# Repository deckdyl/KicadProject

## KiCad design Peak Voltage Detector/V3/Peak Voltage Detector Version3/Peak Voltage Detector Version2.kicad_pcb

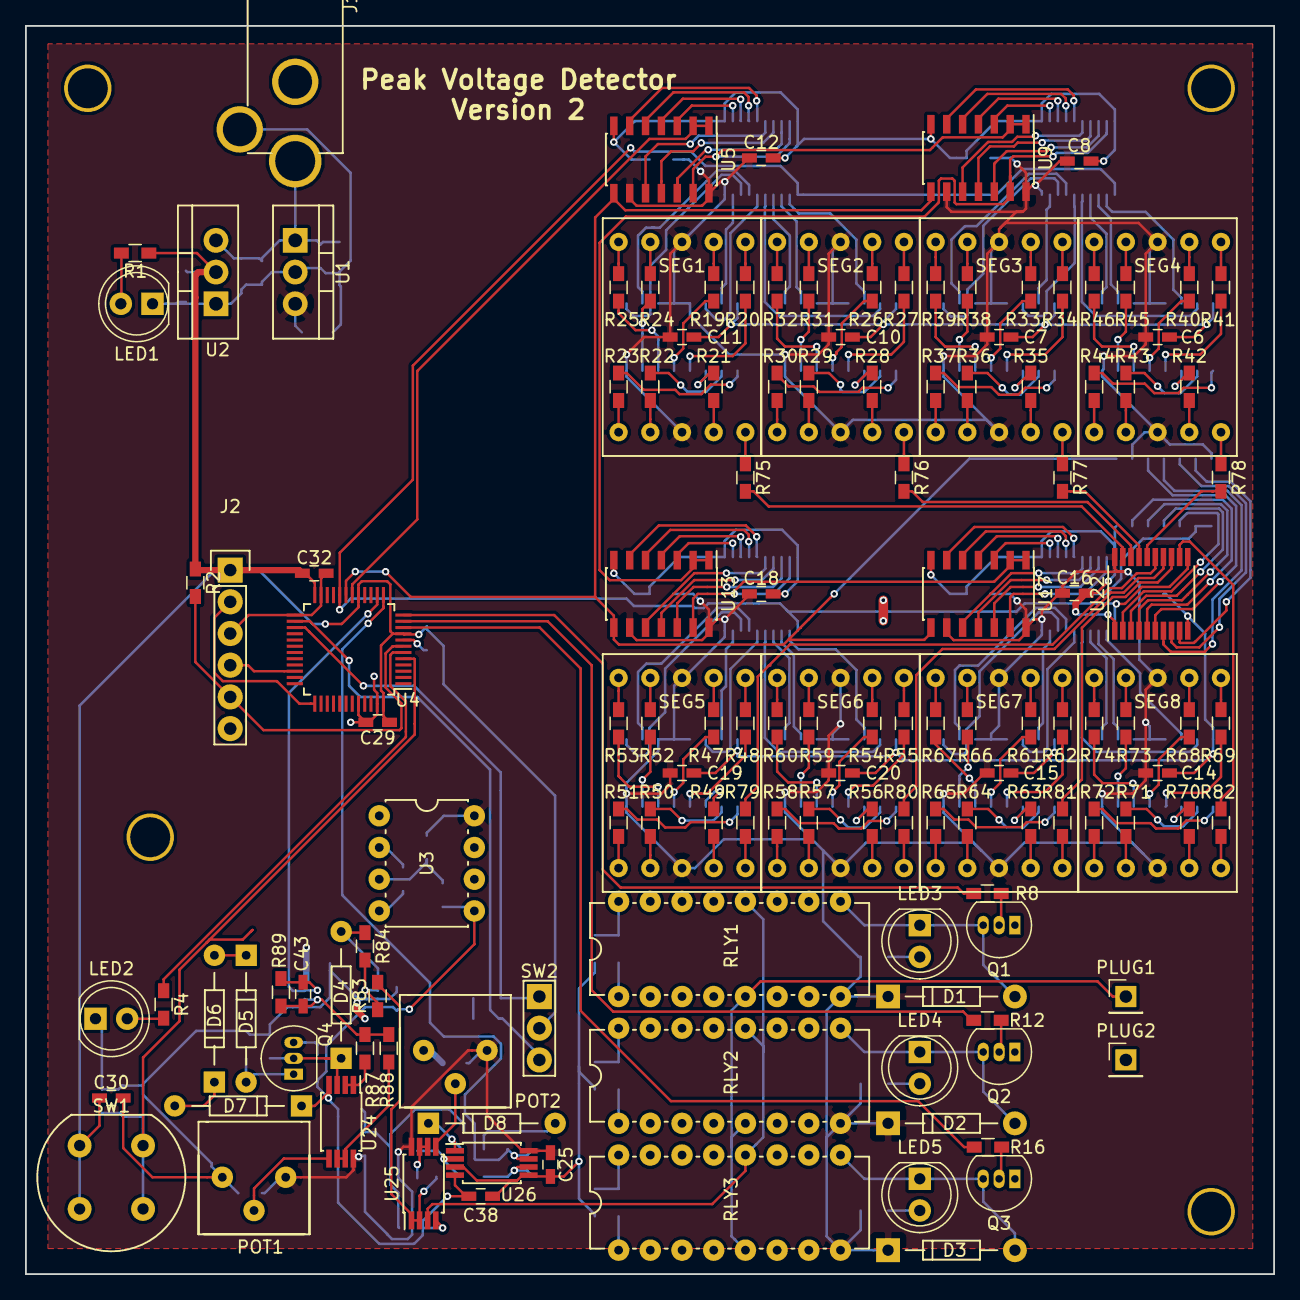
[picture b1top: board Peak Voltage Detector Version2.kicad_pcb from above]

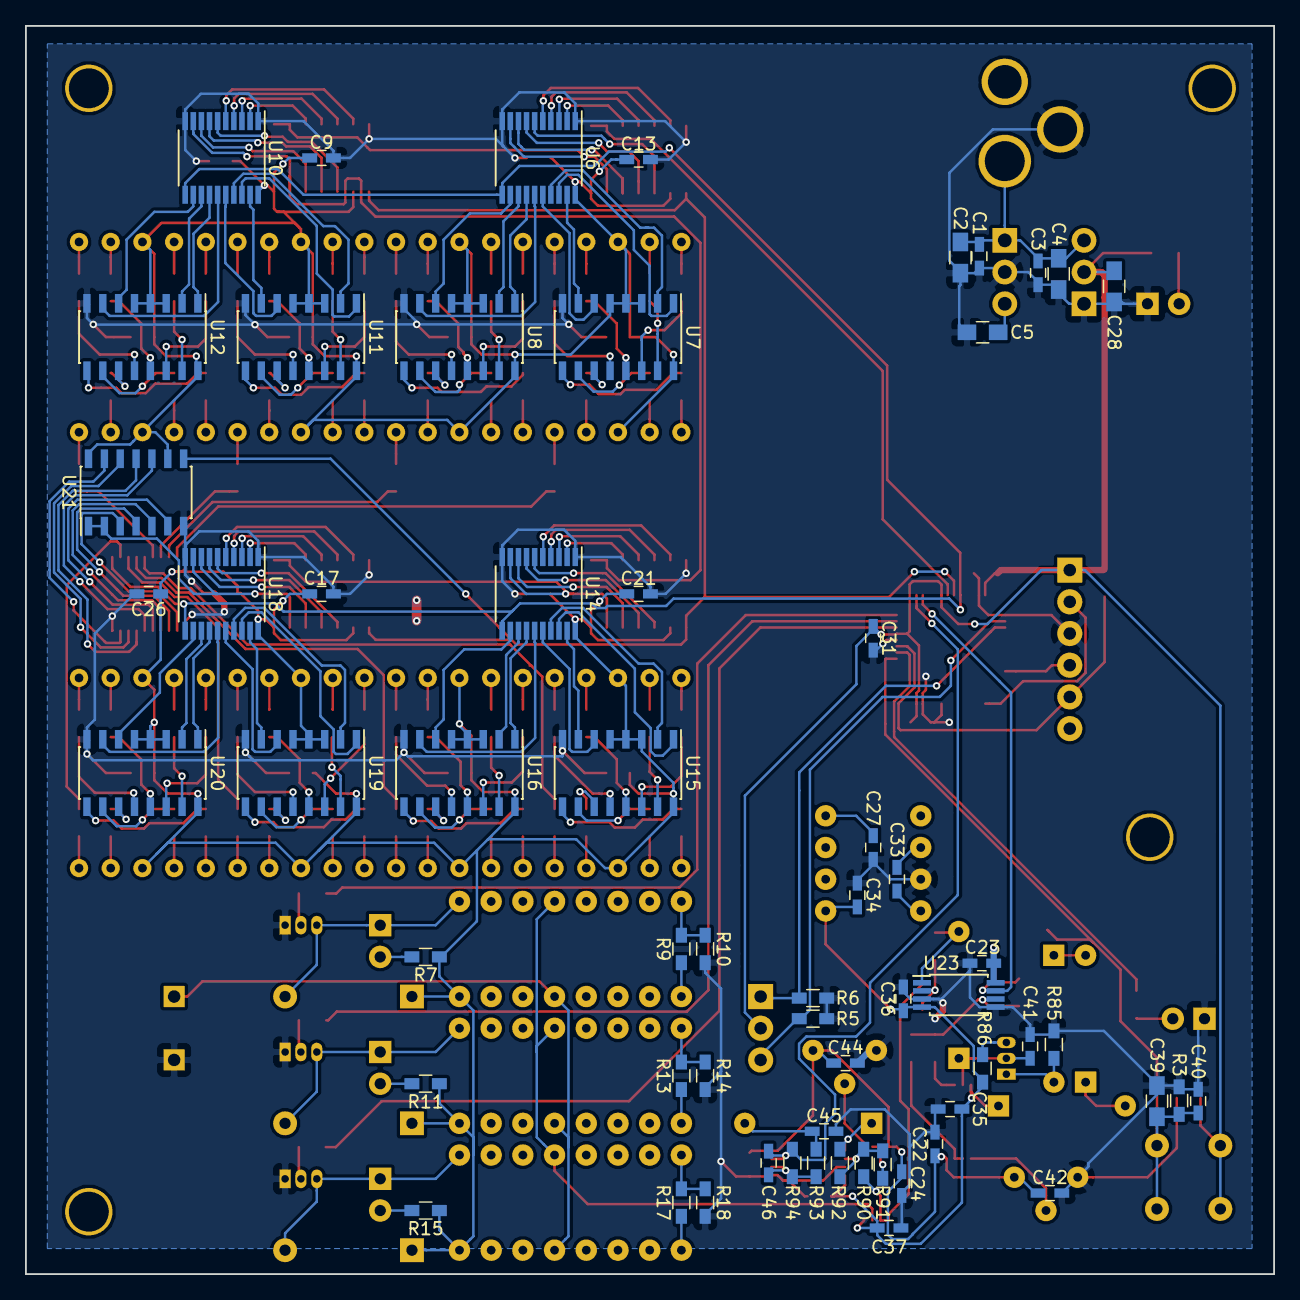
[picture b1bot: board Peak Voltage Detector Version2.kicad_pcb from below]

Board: 2 copper layers, 100.0 x 100.0 mm, 202 parts (61 on the bottom side), 259 nets.

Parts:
C1, C3, C6, C7, C8, C9, C10, C11, C12, C13, C14, C15, C16, C17, C18, C19, C20, C21, C22, C23, C24, C25, C26, C27, C29, C30, C31, C32, C35, C36, C37, C38, C40, C42, C43, C44: 100nF; C_0603_HandSoldering
C2, C4, C5, C28, C39: 22uF; C_0805_HandSoldering
C33, C34: 10uF; C_0603_HandSoldering
C41, C45, C46: 470nF; C_0603_HandSoldering
D1, D2, D3: 1N4001; 1N5818
D4, D5, D6, D7, D8: 1N914; 1N4148
J1: POWER; Power_Socket_2.1mm
J2: ST-Link; Pin_Header_Straight_1x06
LED1: PowerLED; LED_D5.0mm_FlatTop
LED2: CaptureLED; LED_D5.0mm_FlatTop
LED3: HighVoltageLED; LED_D5.0mm_FlatTop
LED4: MidVoltageLED; LED_D5.0mm_FlatTop
LED5: LowVoltageLED; LED_D5.0mm_FlatTop
PLUG1: Vin; Pin_Header_Straight_1x01_Pitch2.54mm
PLUG2: GND; Pin_Header_Straight_1x01_Pitch2.54mm
POT1, POT2: 10kΩ; Potentiometer_Bourns_3386
Q1, Q2, Q3, Q4: 2N3904; TO-92_Inline_Narrow_Oval
R1, R4: 150Ω; R_0603_HandSoldering
R2, R3, R5, R6: 10kΩ; R_0603_HandSoldering
R7, R11, R15: 270Ω; R_0603_HandSoldering
R8, R12, R16: 1kΩ; R_0603_HandSoldering
R9: 4.02MΩ; R_0603_HandSoldering
R10: 33kΩ; R_0603_HandSoldering
R13: 36.5kΩ; R_0603_HandSoldering
R14: 3.3kΩ; R_0603_HandSoldering
R17: 1.2kΩ; R_0603_HandSoldering
R18: 5.6kΩ; R_0603_HandSoldering
R19, R20, R21, R22, R23, R24, R25, R26, R27, R28, R29, R30, R31, R32, R33, R34, R35, R36, R37, R38, R39, R40, R41, R42, R43, R44, R45, R46, R47, R48, R49, R50, R51, R52, R53, R54, R55, R56, R57, R58, R59, R60, R61, R62, R63, R64, R65, R66, R67, R68, R69, R70, R71, R72, R73, R74, R75, R76, R77, R78, R79, R80, R81, R82: 330Ω; R_0603_HandSoldering
R83, R84, R85, R86, R87, R88, R89, R90, R91, R92, R93, R94: 100kΩ; R_0603_HandSoldering
RLY1: HighVoltage; IC_PDIP_16pin
RLY2: MidVoltage; IC_PDIP_16pin
RLY3: LowVoltage; IC_PDIP_16pin
SEG1, SEG2, SEG3, SEG4, SEG5, SEG6, SEG7, SEG8: 7Segment_CA; 7Seg_small
SW1: SW_Push_Dual; Round_Button
SW2: Voltage Select; Pin_Header_Straight_1x03
U1: L7805; TO-220_Neutral123_Vertical
U2: LD1117; TO-220_Neutral123_Vertical
U3: TC962; IC_PDIP_8pin
U4: STM32F373C8T6; LQFP-48_7x7mm_Pitch0.5mm
U5, U9, U13, U17, U21: 74LS164; SOIC-14_3.9x8.7mm_Pitch1.27mm
U6, U10, U14, U18, U22: 74HCT573; TSSOP-20_4.4x6.5mm_Pitch0.65mm
U7, U8, U11, U12, U15, U16, U19, U20: 74LS47; SOIC-16_3.9x9.9mm_Pitch1.27mm
U23, U24, U25, U26: LM4565; TSSOP-8_4.4x3mm_Pitch0.65mm

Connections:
+3V3: C28.1, C29.1, C30.1, C31.1, C32.1, J2.1, R1.1, R2.1, SW1.1, SW2.2, U2.2, U4.9, U4.17, U4.24, U4.48
+5V: C5.1, C6.1, C7.1, C8.1, C9.1, C10.1, C11.1, C12.1, C13.1, C14.1, C15.1, C16.1, C17.1, C18.1, C19.1, C20.1, C21.1, C22.1, C23.1, C24.1, C25.1, C26.1, C27.1, C42.1, C44.1, D1.1, D2.1, D3.1, POT1.1, POT2.1, R7.1, R11.1, R15.1, RLY1.8, RLY2.8, RLY3.8, SEG1.3,8, SEG2.3,8, SEG3.3,8, SEG4.3,8, SEG5.3,8, SEG6.3,8, SEG7.3,8, SEG8.3,8, U1.3, U3.8, U5.9, U5.14, U6.20, U7.3, U7.4, U7.5, U7.16, U8.3, U8.4, U8.5, U8.16, U9.9, U9.14, U10.20, U11.3, U11.4, U11.5, U11.16, U12.3, U12.4, U12.5, U12.16, U13.9, U13.14, U14.20, U15.3, U15.4, U15.5, U15.16, U16.3, U16.4, U16.5, U16.16, U17.9, U17.14, U18.20, U19.3, U19.4, U19.5, U19.16, U20.3, U20.4, U20.5, U20.16, U21.9, U21.14, U22.20, U23.8, U24.8, U25.8, U26.8
-5V: C34.2, C35.1, C36.1, C37.1, C38.1, D7.1, R86.1, U3.5, U23.4, U24.4, U25.4, U26.4
/CAPTURE_BUTTON: C39.1, C40.1, R3.1, SW1.2, U4.5
/DISPLAY_CLOCK: U4.19, U5.8, U9.8, U13.8, U17.8, U21.8
/DISPLAY_DATA: U4.18, U5.1, U5.2
/HIGH_VOLTAGE_RELAY: R8.1, U4.12
/HighVoltageSelect: R6.1, SW2.1, U4.27
/LOW_VOLTAGE_RELAY: R16.1, U4.10
/LowVoltageSelect: R5.1, SW2.3, U4.26
/MID_VOLTAGE_RELAY: R12.1, U4.11
/MaxVoltage: C46.1, R94.1, U4.13, U26.7
/MinVoltage: C43.1, R89.1, U4.14, U23.7
/VoltageRangeSelection/OutputVoltage: R83.2, R90.2, U25.1, U25.2
/VoltageRangeSelection/Vin: PLUG1.1, RLY1.5, RLY2.5, RLY3.5
DP1: R75.1, SEG1.5
DP2: R76.1, SEG2.5
DP3: R77.1, SEG3.5
DP4: R78.1, SEG4.5
DP5: R79.1, SEG5.5
DP6: R80.1, SEG6.5
DP7: R81.1, SEG7.5
DP8: R82.1, SEG8.5
GND: C1.2, C2.2, C3.2, C4.2, C5.2, C6.2, C7.2, C8.2, C9.2, C10.2, C11.2, C12.2, C13.2, C14.2, C15.2, C16.2, C17.2, C18.2, C19.2, C20.2, C21.2, C22.2, C23.2, C24.2, C25.2, C26.2, C27.2, C28.2, C29.2, C30.2, C31.2, C32.2, C34.1, C35.2, C36.2, C37.2, C38.2, C39.2, C40.2, C41.2, C42.2, C44.2, C45.2, J1.2, J2.3, LED1.1, LED2.1, PLUG2.1, POT1.3, POT2.3, Q1.1, Q2.1, Q3.1, R3.2, R5.2, R6.2, R10.2, R14.2, R18.2, R85.2, U1.2, U2.1, U3.3, U4.8, U4.23, U4.25, U4.44, U4.47, U5.7, U6.1, U6.10, U7.8, U8.8, U9.7, U10.1, U10.10, U11.8, U12.8, U13.7, U14.1, U14.10, U15.8, U16.8, U17.7, U18.1, U18.10, U19.8, U20.8, U21.7, U22.1, U22.10, U23.3, U23.5, U26.3, U26.5
LATCH: U4.20, U6.11, U10.11, U14.11, U18.11, U22.11
NRST: J2.5, R2.2, U4.7
unnamed: C1.1, C2.1, C3.1, C4.1, J1.1, U1.1, U2.3
unnamed: C33.1, U3.2
unnamed: C33.2, U3.4
unnamed: C41.1, D4.1, Q4.2, U24.3
unnamed: C43.2, R87.1, R88.1, R89.2, U23.6
unnamed: C45.1, D8.2, R93.2
unnamed: C46.2, R93.1, R94.2, U26.6
unnamed: D1.2, LED3.1, Q1.3, RLY1.9
unnamed: D2.2, LED4.1, Q2.3, RLY2.9
unnamed: D3.2, LED5.1, Q3.3, RLY3.9
unnamed: D4.2, R84.1, U23.1
unnamed: D5.1, D6.2
unnamed: D5.2, Q4.1, R85.1
unnamed: D6.1, D7.2
unnamed: D8.1, R92.1, U26.1
unnamed: LED1.2, R1.2
unnamed: LED2.2, R4.2
unnamed: LED3.2, R7.2
unnamed: LED4.2, R11.2
unnamed: LED5.2, R15.2
unnamed: POT1.2, U24.5
unnamed: POT2.2, U25.5
unnamed: Q1.2, R8.2
unnamed: Q2.2, R12.2
unnamed: Q3.2, R16.2
unnamed: Q4.3, R86.2
unnamed: R4.1, U4.6
unnamed: R9.1, RLY1.1
unnamed: R9.2, R10.1, RLY1.16
unnamed: R13.1, RLY2.1
unnamed: R13.2, R14.1, RLY2.16
unnamed: R17.1, RLY3.1
unnamed: R17.2, R18.1, RLY3.16
unnamed: R19.1, SEG1.7
unnamed: R19.2, U7.13
unnamed: R20.1, SEG1.6
unnamed: R20.2, U7.12
unnamed: R21.1, SEG1.4
unnamed: R21.2, U7.11
unnamed: R22.1, SEG1.2
unnamed: R22.2, U7.10
unnamed: R23.1, SEG1.1
unnamed: R23.2, U7.9
unnamed: R24.1, SEG1.9
unnamed: R24.2, U7.15
unnamed: R25.1, SEG1.10
unnamed: R25.2, U7.14
unnamed: R26.1, SEG2.7
unnamed: R26.2, U8.13
unnamed: R27.1, SEG2.6
unnamed: R27.2, U8.12
unnamed: R28.1, SEG2.4
unnamed: R28.2, U8.11
unnamed: R29.1, SEG2.2
unnamed: R29.2, U8.10
unnamed: R30.1, SEG2.1
unnamed: R30.2, U8.9
unnamed: R31.1, SEG2.9
unnamed: R31.2, U8.15
unnamed: R32.1, SEG2.10
unnamed: R32.2, U8.14
unnamed: R33.1, SEG3.7
unnamed: R33.2, U11.13
unnamed: R34.1, SEG3.6
unnamed: R34.2, U11.12
unnamed: R35.1, SEG3.4
unnamed: R35.2, U11.11
unnamed: R36.1, SEG3.2
unnamed: R36.2, U11.10
unnamed: R37.1, SEG3.1
unnamed: R37.2, U11.9
unnamed: R38.1, SEG3.9
unnamed: R38.2, U11.15
unnamed: R39.1, SEG3.10
unnamed: R39.2, U11.14
unnamed: R40.1, SEG4.7
unnamed: R40.2, U12.13
unnamed: R41.1, SEG4.6
unnamed: R41.2, U12.12
unnamed: R42.1, SEG4.4
unnamed: R42.2, U12.11
unnamed: R43.1, SEG4.2
unnamed: R43.2, U12.10
unnamed: R44.1, SEG4.1
unnamed: R44.2, U12.9
unnamed: R45.1, SEG4.9
unnamed: R45.2, U12.15
unnamed: R46.1, SEG4.10
unnamed: R46.2, U12.14
unnamed: R47.1, SEG5.7
unnamed: R47.2, U15.13
unnamed: R48.1, SEG5.6
unnamed: R48.2, U15.12
unnamed: R49.1, SEG5.4
unnamed: R49.2, U15.11
unnamed: R50.1, SEG5.2
unnamed: R50.2, U15.10
unnamed: R51.1, SEG5.1
unnamed: R51.2, U15.9
unnamed: R52.1, SEG5.9
unnamed: R52.2, U15.15
unnamed: R53.1, SEG5.10
unnamed: R53.2, U15.14
unnamed: R54.1, SEG6.7
unnamed: R54.2, U16.13
unnamed: R55.1, SEG6.6
unnamed: R55.2, U16.12
unnamed: R56.1, SEG6.4
unnamed: R56.2, U16.11
unnamed: R57.1, SEG6.2
unnamed: R57.2, U16.10
unnamed: R58.1, SEG6.1
unnamed: R58.2, U16.9
unnamed: R59.1, SEG6.9
unnamed: R59.2, U16.15
unnamed: R60.1, SEG6.10
unnamed: R60.2, U16.14
unnamed: R61.1, SEG7.7
unnamed: R61.2, U19.13
unnamed: R62.1, SEG7.6
unnamed: R62.2, U19.12
unnamed: R63.1, SEG7.4
unnamed: R63.2, U19.11
unnamed: R64.1, SEG7.2
unnamed: R64.2, U19.10
unnamed: R65.1, SEG7.1
unnamed: R65.2, U19.9
unnamed: R66.1, SEG7.9
unnamed: R66.2, U19.15
unnamed: R67.1, SEG7.10
unnamed: R67.2, U19.14
unnamed: R68.1, SEG8.7
unnamed: R68.2, U20.13
unnamed: R69.1, SEG8.6
unnamed: R69.2, U20.12
unnamed: R70.1, SEG8.4
unnamed: R70.2, U20.11
unnamed: R71.1, SEG8.2
unnamed: R71.2, U20.10
unnamed: R72.1, SEG8.1
unnamed: R72.2, U20.9
unnamed: R73.1, SEG8.9
unnamed: R73.2, U20.15
unnamed: R74.1, SEG8.10
unnamed: R74.2, U20.14
unnamed: R75.2, U22.19
unnamed: R76.2, U22.18
unnamed: R77.2, U22.17
unnamed: R78.2, U22.16
unnamed: R79.2, U22.15
unnamed: R80.2, U22.14
unnamed: R81.2, U22.13
unnamed: R82.2, U22.12
unnamed: R83.1, R84.2, U23.2
unnamed: R87.2, U24.1, U24.2
unnamed: R88.2, U24.6, U24.7
unnamed: R90.1, R91.1, R92.2, U26.2
unnamed: R91.2, U25.6, U25.7
unnamed: RLY1.12, RLY2.12, RLY3.12, U25.3
unnamed: U5.3, U6.2
unnamed: U5.4, U6.3
unnamed: U5.5, U6.4
unnamed: U5.6, U6.5
unnamed: U5.10, U6.6
unnamed: U5.11, U6.7
unnamed: U5.12, U6.8
unnamed: U5.13, U6.9, U9.1, U9.2
unnamed: U6.12, U8.6
unnamed: U6.13, U8.2
unnamed: U6.14, U8.1
unnamed: U6.15, U8.7
unnamed: U6.16, U7.6
unnamed: U6.17, U7.2
unnamed: U6.18, U7.1
unnamed: U6.19, U7.7
unnamed: U9.3, U10.2
unnamed: U9.4, U10.3
unnamed: U9.5, U10.4
unnamed: U9.6, U10.5
unnamed: U9.10, U10.6
unnamed: U9.11, U10.7
unnamed: U9.12, U10.8
unnamed: U9.13, U10.9, U13.1, U13.2
unnamed: U10.12, U12.6
unnamed: U10.13, U12.2
unnamed: U10.14, U12.1
unnamed: U10.15, U12.7
unnamed: U10.16, U11.6
unnamed: U10.17, U11.2
unnamed: U10.18, U11.1
unnamed: U10.19, U11.7
unnamed: U13.3, U14.2
unnamed: U13.4, U14.3
unnamed: U13.5, U14.4
unnamed: U13.6, U14.5
unnamed: U13.10, U14.6
unnamed: U13.11, U14.7
unnamed: U13.12, U14.8
unnamed: U13.13, U14.9, U17.1, U17.2
unnamed: U14.12, U16.6
unnamed: U14.13, U16.2
unnamed: U14.14, U16.1
unnamed: U14.15, U16.7
unnamed: U14.16, U15.6
unnamed: U14.17, U15.2
unnamed: U14.18, U15.1
unnamed: U14.19, U15.7
unnamed: U17.3, U18.2
unnamed: U17.4, U18.3
unnamed: U17.5, U18.4
unnamed: U17.6, U18.5
unnamed: U17.10, U18.6
unnamed: U17.11, U18.7
unnamed: U17.12, U18.8
unnamed: U17.13, U18.9, U21.1, U21.2
unnamed: U18.12, U20.6
unnamed: U18.13, U20.2
unnamed: U18.14, U20.1
unnamed: U18.15, U20.7
unnamed: U18.16, U19.6
unnamed: U18.17, U19.2
unnamed: U18.18, U19.1
unnamed: U18.19, U19.7
unnamed: U21.3, U22.2
unnamed: U21.4, U22.3
unnamed: U21.5, U22.4
unnamed: U21.6, U22.5
unnamed: U21.10, U22.6
unnamed: U21.11, U22.7
unnamed: U21.12, U22.8
unnamed: U21.13, U22.9
SWDCLK: J2.2, U4.37
SWDIO: J2.4, U4.34

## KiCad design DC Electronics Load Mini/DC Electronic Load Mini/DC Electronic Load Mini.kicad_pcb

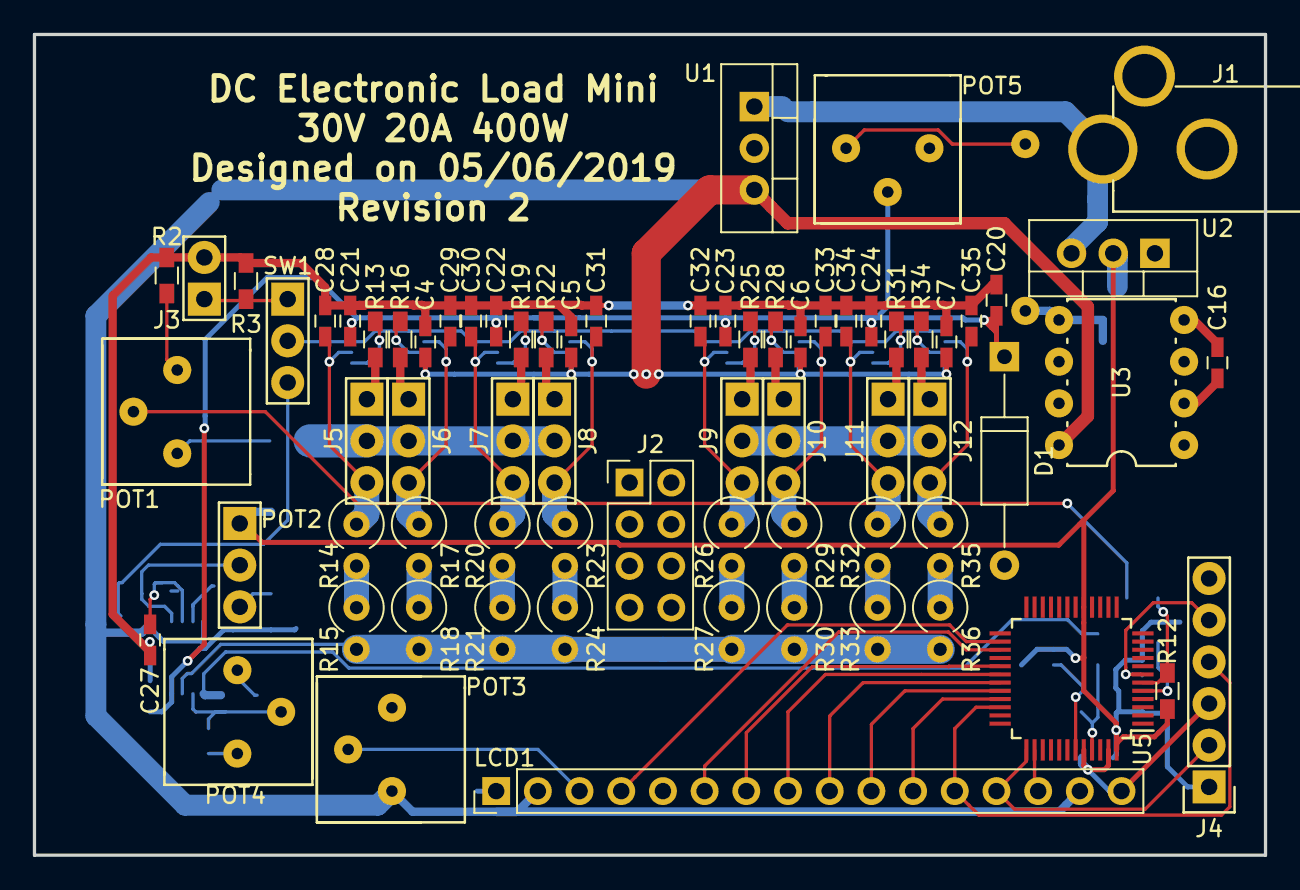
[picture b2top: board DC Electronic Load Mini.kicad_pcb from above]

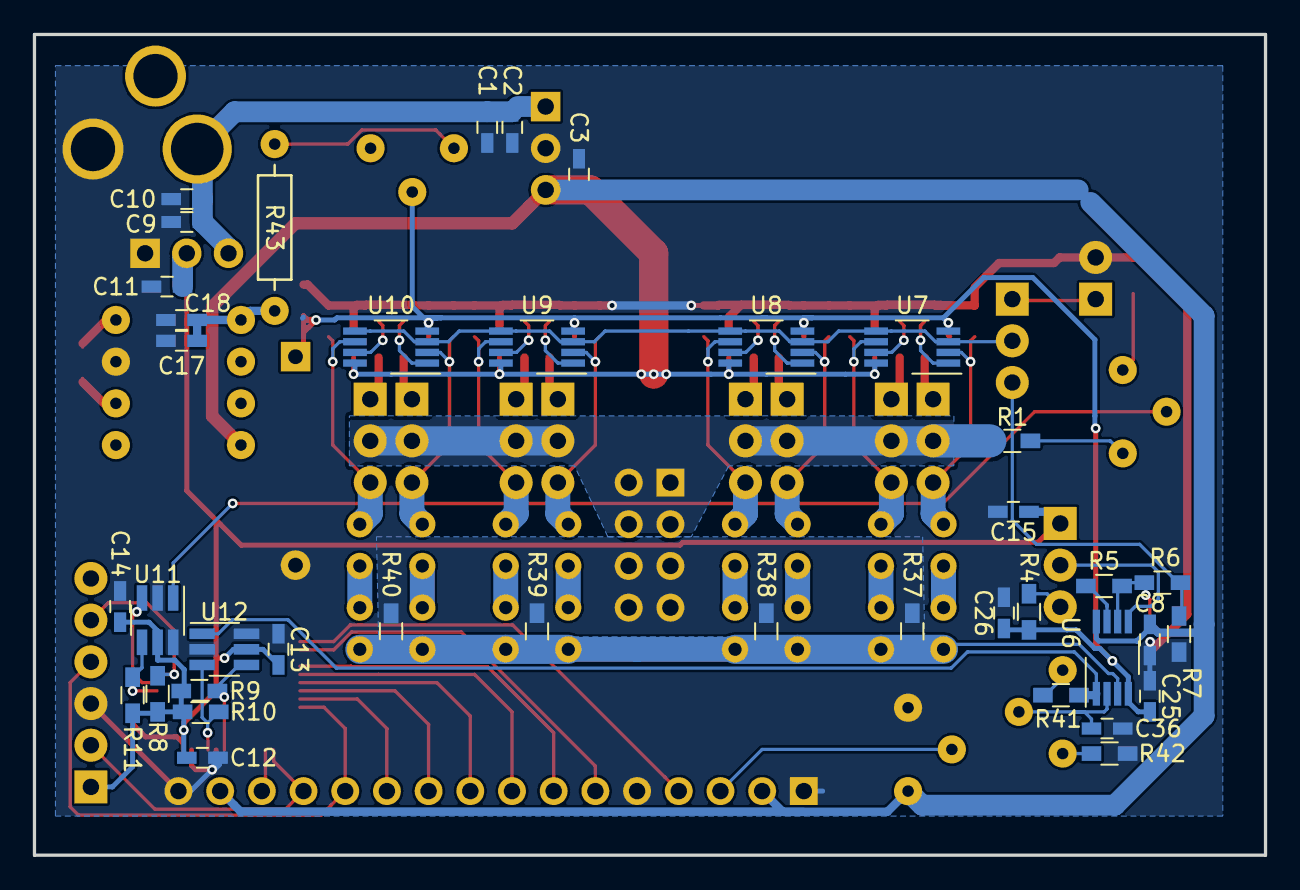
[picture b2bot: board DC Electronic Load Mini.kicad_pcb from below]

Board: 2 copper layers, 75.0 x 50.0 mm, 109 parts (39 on the bottom side), 73 nets.

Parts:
C1, C3, C9, C11, C16, C17, C20: 10uF; C_0603_HandSoldering
C2, C4, C5, C6, C7, C8, C10, C12, C13, C14, C15, C18, C21, C22, C23, C24, C25, C26, C27: 100nF; C_0603_HandSoldering
C28, C29, C30, C31, C32, C33, C34, C35, C36: 10nF; C_0603_HandSoldering
D1: 1N914; D_A-405_P12.70mm_Horizontal
J1: Power; Power_Socket_2.1mm
J2: Vin; Pin_Header_Straight_2x04_Pitch2.54mm
J3: ExternalVset; Pin_Header_Straight_1x02
J4: ST-LINK; Pin_Header_Straight_1x06
J5: MOSFET 1; Pin_Header_Straight_1x03
J6: MOSFET 2; Pin_Header_Straight_1x03
J7: MOSFET 3; Pin_Header_Straight_1x03
J8: MOSFET 4; Pin_Header_Straight_1x03
J9: MOSFET 5; Pin_Header_Straight_1x03
J10: MOSFET 6; Pin_Header_Straight_1x03
J11: MOSFET 7; Pin_Header_Straight_1x03
J12: MOSFET 8; Pin_Header_Straight_1x03
LCD1: LCD1602; Pin_Header_Straight_1x16_Pitch2.54mm
POT1: 500Ω; Potentiometer_Bourns_3386
POT2: 50kΩ; Pin_Header_Straight_1x03
POT3: 10kΩ; Potentiometer_Bourns_3386
POT4: 200Ω; Potentiometer_Bourns_3386
POT5: 100Ω; Potentiometer_Bourns_3386
R1: 29kΩ; R_0603_HandSoldering
R2: 1k8Ω; R_0603_HandSoldering
R3, R8, R9, R10, R11, R12: 10kΩ; R_0603_HandSoldering
R4: 6k2Ω; R_0603_HandSoldering
R5, R13, R16, R19, R22, R25, R28, R31, R34: 100Ω; R_0603_HandSoldering
R6: 910Ω; R_0603_HandSoldering
R7: 220Ω; R_0603_HandSoldering
R14, R15, R17, R18, R20, R21, R23, R24, R26, R27, R29, R30, R32, R33, R35, R36: 0Ω1; R_Axial_DIN0309_L9.0mm_D3.2mm_P2.54mm_Vertical
R37, R38, R39, R40: 0Ω02; R_0603_HandSoldering
R41: 18kΩ; R_0603_HandSoldering
R42: 820Ω; R_0603_HandSoldering
R43: 50Ω; Resistor-0.25W
SW1: SW_SPDT; Pin_Header_Straight_1x03
U1: L7805; TO-220-3_Vertical
U2: LD1117; TO-220-3_Vertical
U3: TC962; IC_PDIP_8pin
U5: STM32F373C8T6; LQFP-48_7x7mm_Pitch0.5mm
U6, U7, U8, U9, U10: LMP2022; VSSOP-8_3.0x3.0mm_Pitch0.65mm
U11, U12: MCP3425; SOT-23-6_Handsoldering

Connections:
+3V3: C11.1, C12.1, C13.1, C14.1, C15.1, J4.1, POT2.1, R8.1, R9.1, R10.1, R11.1, R12.1, U2.2, U5.17, U5.48, U11.5, U12.5
+5V: C3.1, C4.1, C5.1, C6.1, C7.1, C8.1, LCD1.2, LCD1.15, POT3.1, U1.3, U3.8, U6.8, U7.8, U8.8, U9.8, U10.8
-0V5: C20.1, C21.1, C22.1, C23.1, C24.1, C25.1, C26.1, D1.1, POT5.2, R4.2, U6.4, U7.4, U8.4, U9.4, U10.4
-5V: C17.2, C18.2, R43.2, U3.5
/CurrentADC: R41.1, U6.1, U12.1
/LCD_DB0: LCD1.7, U5.29
/LCD_DB1: LCD1.8, U5.30
/LCD_DB2: LCD1.9, U5.31
/LCD_DB3: LCD1.10, U5.32
/LCD_DB4: LCD1.11, U5.33
/LCD_DB5: J4.4, LCD1.12, U5.34
/LCD_DB6: J4.2, LCD1.13, U5.37
/LCD_DB7: LCD1.14, U5.38
/LCD_EN: LCD1.6, U5.27
/LCD_RS: LCD1.4, U5.26
/LoadControl/I_Sense: R15.2, R18.2, R21.2, R24.2, R27.2, R30.2, R33.2, R36.2, R37.1, R38.1, R39.1, R40.1, U6.3
/LoadControl/Vin: J2.1, J2.2, J2.3, J2.4, J5.2, J6.2, J7.2, J8.2, J9.2, J10.2, J11.2, J12.2, R1.1
/NRST: J4.5, R8.2, U5.7
/VoltageADC: POT1.2, U11.1
/Vset: SW1.2, U7.3, U7.5, U8.3, U8.5, U9.3, U9.5, U10.3, U10.5
GND: C1.2, C2.2, C3.2, C4.2, C5.2, C6.2, C7.2, C8.2, C9.2, C10.2, C11.2, C12.2, C13.2, C14.2, C15.2, C17.1, C18.1, C20.2, C21.2, C22.2, C23.2, C24.2, C25.2, C26.2, C27.2, C28.2, C29.2, C30.2, C31.2, C32.2, C33.2, C34.2, C35.2, C36.2, D1.2, J1.2, J2.5, J2.6, J2.7, J2.8, J3.2, J4.3, LCD1.1, LCD1.5, LCD1.16, POT3.3, R2.2, R3.2, R7.2, R37.2, R38.2, R39.2, R40.2, R42.2, U1.2, U2.1, U3.3, U5.44, U5.47, U11.2, U11.6, U12.2, U12.6
unnamed: C1.1, C2.1, C9.1, C10.1, J1.1, U1.1, U2.3
unnamed: C16.1, U3.2
unnamed: C16.2, U3.4
unnamed: C27.1, R5.1, R6.2, U6.6
unnamed: C28.1, J5.3, R14.1, U7.2
unnamed: C29.1, J6.3, R17.1, U7.6
unnamed: C30.1, J7.3, R20.1, U8.2
unnamed: C31.1, J8.3, R23.1, U8.6
unnamed: C32.1, J9.3, R26.1, U9.2
unnamed: C33.1, J10.3, R29.1, U9.6
unnamed: C34.1, J11.3, R32.1, U10.2
unnamed: C35.1, J12.3, R35.1, U10.6
unnamed: C36.1, POT4.2, U6.2
unnamed: J3.1, R3.1, SW1.1
unnamed: J5.1, R13.1
unnamed: J6.1, R16.1
unnamed: J7.1, R19.1
unnamed: J8.1, R22.1
unnamed: J9.1, R25.1
unnamed: J10.1, R28.1
unnamed: J11.1, R31.1
unnamed: J12.1, R34.1
unnamed: LCD1.3, POT3.2
unnamed: POT1.1, R1.2
unnamed: POT1.3, R2.1
unnamed: POT2.2, U6.5
unnamed: POT2.3, R4.1
unnamed: POT4.1, R41.2
unnamed: POT4.3, R42.1
unnamed: POT5.3, R43.1
unnamed: R5.2, U6.7
unnamed: R6.1, R7.1, SW1.3
unnamed: R9.2, U5.43, U12.4
unnamed: R10.2, U5.45, U12.3
unnamed: R11.2, U5.5, U11.4
unnamed: R12.2, U5.6, U11.3
unnamed: R13.2, U7.1
unnamed: R14.2, R15.1
unnamed: R16.2, U7.7
unnamed: R17.2, R18.1
unnamed: R19.2, U8.1
unnamed: R20.2, R21.1
unnamed: R22.2, U8.7
unnamed: R23.2, R24.1
unnamed: R25.2, U9.1
unnamed: R26.2, R27.1
unnamed: R28.2, U9.7
unnamed: R29.2, R30.1
unnamed: R31.2, U10.1
unnamed: R32.2, R33.1
unnamed: R34.2, U10.7
unnamed: R35.2, R36.1

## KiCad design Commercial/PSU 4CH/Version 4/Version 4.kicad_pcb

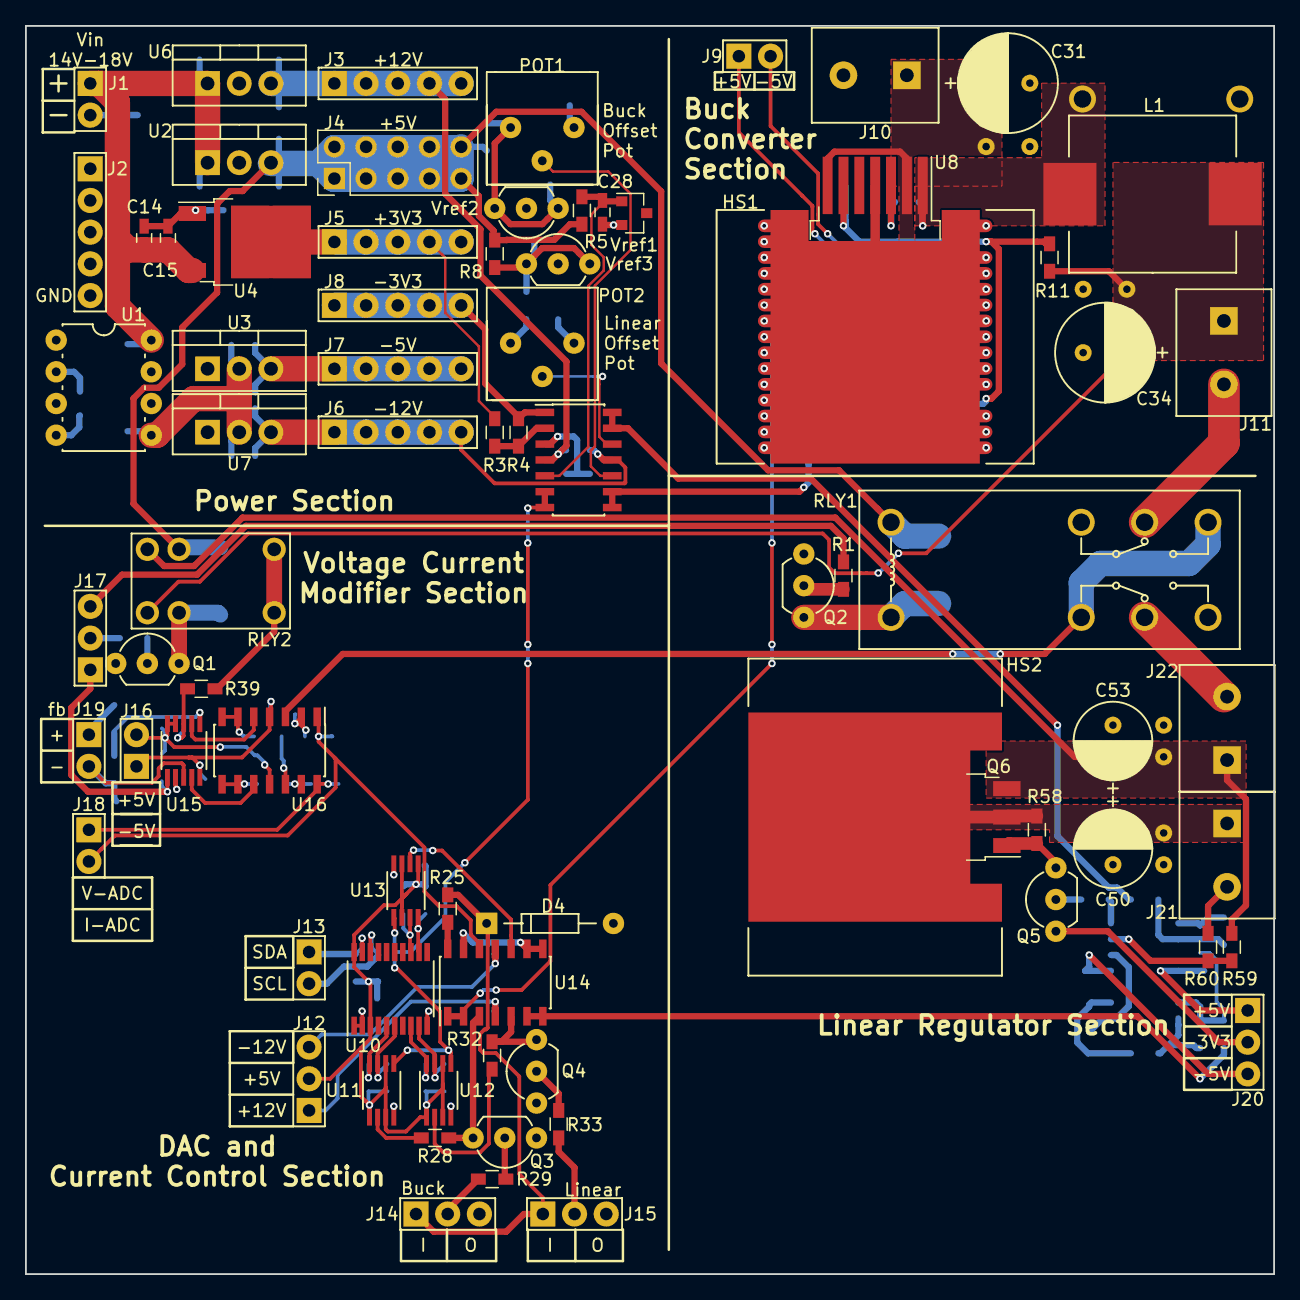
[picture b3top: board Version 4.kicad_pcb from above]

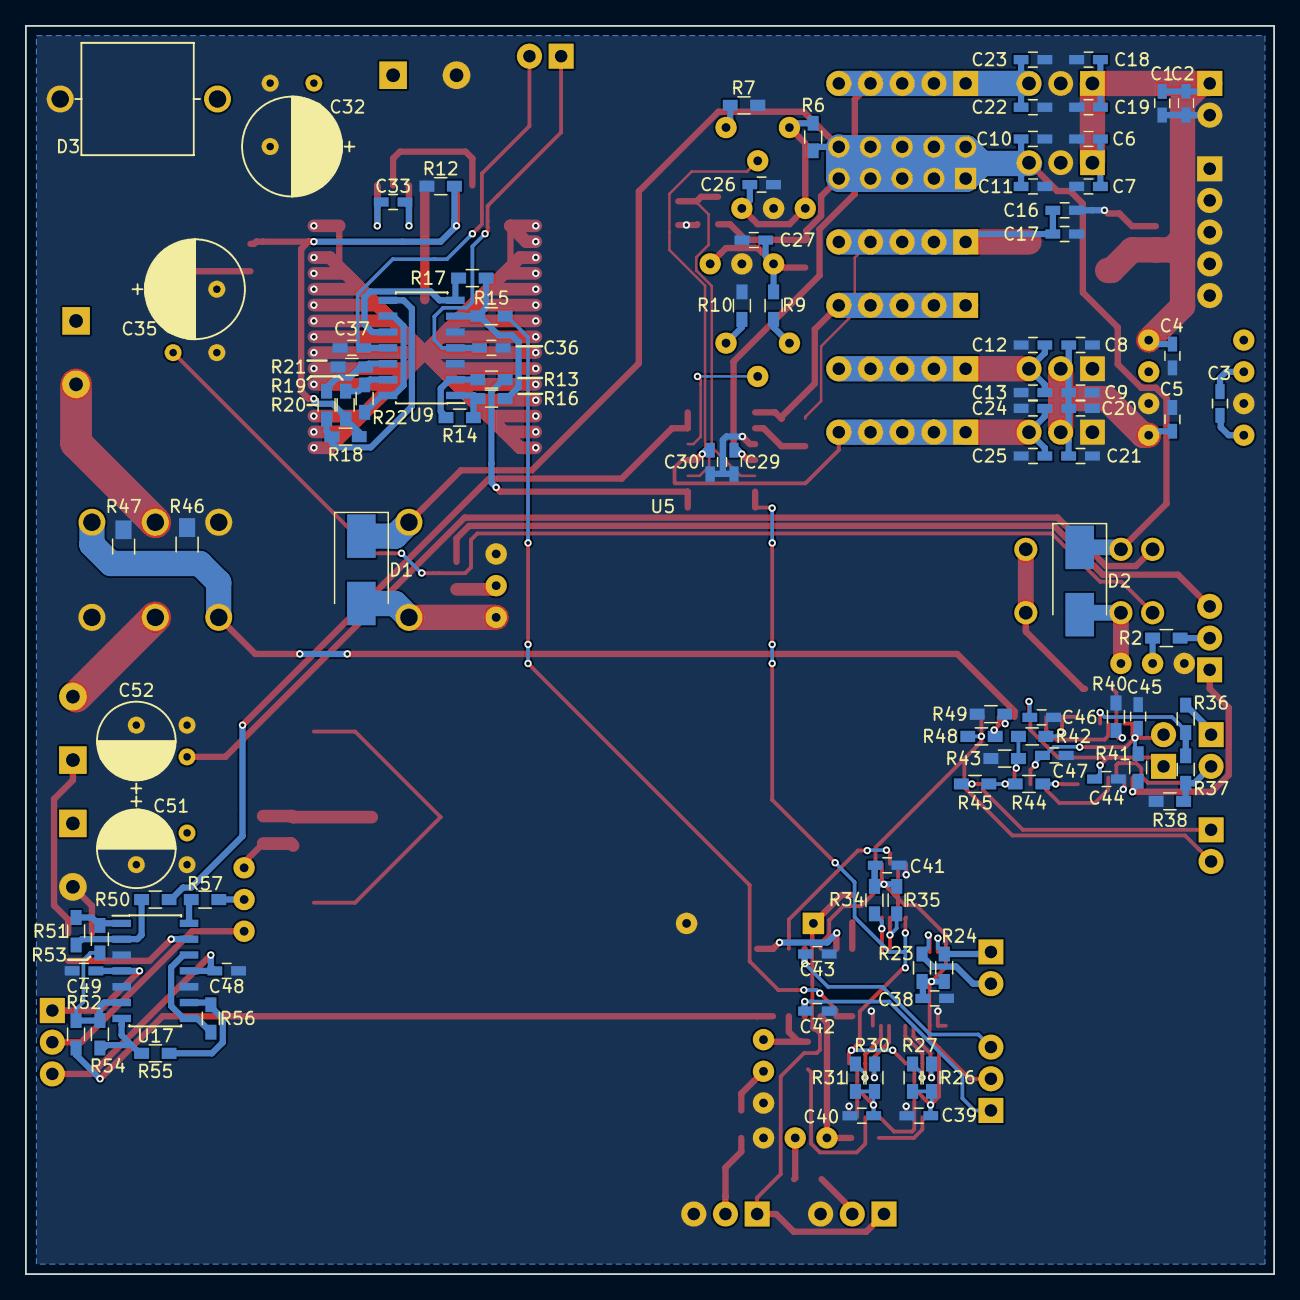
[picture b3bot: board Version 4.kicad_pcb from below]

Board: 2 copper layers, 100.0 x 100.0 mm, 172 parts (96 on the bottom side), 104 nets.

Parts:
C1, C3, C4, C5, C6, C8, C10, C12, C14, C16, C18, C20, C22, C24: 10uF; C_0603_HandSoldering
C2, C7, C9, C11, C13, C15, C17, C19, C21, C23, C25, C26, C27, C28, C29, C30, C33, C36, C37, C38, C39, C40, C41, C42, C43, C44, C45, C46, C47, C48, C49: 100nF; C_0603_HandSoldering
C31, C32, C34, C35: 100uF; Radial-8mm-Pitch-3.5mm-Pin-0.6
C50, C51, C52, C53: 47uF; Radial-6mm-Pitch-2.5mm-Pin-0.6mm
D1, D2: S2A; D_SMB_Handsoldering
D3: 15SQ045; Diode-Radial-9mm-length-9mm-pitch-12.7mm
D4: 1N914; 1N4148
HS1, HS2: Heatsink_Pad; Heatsink_SMD_D2PAK
J1: +14Vin; Pin_Header_Straight_1x02
J2: GND; Pin_Header_Straight_1x05
J3: +12V; Pin_Header_Straight_1x05
J4: +5V; Pin_Header_Straight_2x05_Pitch2.54mm
J5: +3V3; Pin_Header_Straight_1x05
J6: -12V; Pin_Header_Straight_1x05
J7: -5V; Pin_Header_Straight_1x05
J8: -3V3; Pin_Header_Straight_1x05
J9: Buck Power; Pin_Header_Straight_1x02
J10, J21: Vin; Terminal_Block-5mm
J11, J22: Vout; Terminal_Block-5mm
J12: DAC&CC Power; Pin_Header_Straight_1x03
J13: DAC&CC Digital I/O; Pin_Header_Straight_1x02
J14: BuckEnable; Pin_Header_Straight_1x03
J15: LinearEnable; Pin_Header_Straight_1x03
J16: VCMod Power; Pin_Header_Straight_1x02
J17: VCMod Digital I/O; Pin_Header_Straight_1x03
J18: VCMod Analog I/O; Pin_Header_Straight_1x02
J19: Vfb; Pin_Header_Straight_1x02
J20: Linear Power; Pin_Header_Straight_1x03
L1: 22uH; Inductor_SMD_13X13
POT1: 2kΩ; Potentiometer_Bourns_3386
POT2: 1kΩ; Potentiometer_Bourns_3386
Q1, Q2, Q3, Q4, Q5: 2N3904; TO-92_Inline_Wide
Q6: IPD90P03P4L-04; TO-252-3_TabPin2
R1, R2, R6, R8, R49, R58: 1kΩ; R_0603_HandSoldering
R3, R4, R13, R14, R15, R16, R17, R19, R20, R21, R22, R42, R43, R44, R45, R48, R50, R51, R52, R53, R54, R55, R56: 100kΩ; R_0603_HandSoldering
R5: 470Ω; R_0603_HandSoldering
R7: 8.2kΩ; R_0603_HandSoldering
R9: 2.9kΩ; R_0603_HandSoldering
R10: 1.8kΩ; R_0603_HandSoldering
R11, R57, R59: 47kΩ; R_0603_HandSoldering
R12, R18, R60: 4.7kΩ; R_0603_HandSoldering
R23, R24, R25, R26, R27, R28, R29, R30, R31, R32, R33, R34, R35, R37, R38, R40, R41: 10kΩ; R_0603_HandSoldering
R36, R39: 91kΩ; R_0603_HandSoldering
R46, R47: 12mΩ; R_0805_HandSoldering
RLY1: Relay-DPDT; Relay
RLY2: SPDT; Relay-SPDT(FORM-C)
U1: TC962; IC_PDIP_8pin
U2: L7805; TO-220_Neutral123_Vertical
U3: L7905; TO-220_Neutral123_Vertical
U4: NCP1117-3.3; TO-252-2
U5, U9, U14, U16, U17: OPA4277; SOIC-14_3.9x8.7mm_Pitch1.27mm
U6: L7812; TO-220_Neutral123_Vertical
U7: L7912; TO-220_Neutral123_Vertical
U8: LM2678T-ADJ; TO-263-7_TabPin4
U10: PCA9545B; TSSOP-20_4.4x6.5mm_Pitch0.65mm
U11, U12, U13: MAX5215; uMAX-8
U15: MAX4525; uMAX-10
Vref1: LM4050CIM3-4.1; SOT-23
Vref2, Vref3: TL431; TO-92_Inline_Wide

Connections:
+3V3: C16.1, C17.1, J5.1, J5.2, J5.3, J5.4, J5.5, R3.2, U4.2
+5V: C10.1, C11.1, D1.1, D2.1, J4.1, J4.2, J4.3, J4.4, J4.5, J4.6, J4.7, J4.8, J4.9, J4.10, R5.1, R6.1, R8.1, RLY1.Coil+, RLY2.Coil+, U2.3
+12V: C22.1, C23.1, C29.2, J3.1, J3.2, J3.3, J3.4, J3.5, U5.4, U6.3
+VDC: C1.1, C2.1, C4.2, C6.1, C7.1, C14.1, C15.1, C18.1, C19.1, J1.1, U1.8, U2.1, U4.3, U6.1
-3V3: J8.1, J8.2, J8.3, J8.4, J8.5, R4.1, U5.1
-5V: C12.2, C13.2, J7.1, J7.2, J7.3, J7.4, J7.5, U3.3
-12V: C24.2, C25.2, C30.2, J6.1, J6.2, J6.3, J6.4, J6.5, U5.11, U7.3
-VDC: C5.2, C8.2, C9.2, C20.2, C21.2, U1.5, U3.2, U7.2
/+4.096Vref: U5.6, U5.7, U11.1, U12.1, U13.1
/Buck+5V: C36.1, J9.1, U9.4
/Buck-5V: C37.2, J9.2, U9.11
/BuckConverter/Buck1V2fb: R11.2, R12.1, R18.1, R19.2, U8.6
/BuckConverter/BuckOutputGND: J11.2, RLY1.COM1
/BuckOffset: R13.2, U5.8, U5.9
/BuckVout: C34.1, C35.1, J11.1, L1.2, R11.1, RLY2.NO
/Buck_DAC: R15.2, U14.1, U14.2
/CurrentADC: J18.2, R48.1, U14.12, U16.1
/CurrentSelect: J17.3, R1.2
/DAC and Current Control/BuckDisable: J14.2, R29.2
/DAC and Current Control/Buck_SCL: R27.2, U10.6, U11.3
/DAC and Current Control/Buck_SDA: R26.2, U10.5, U11.4
/DAC and Current Control/IsetDACBuffered: U14.8, U14.9, U14.13
/DAC and Current Control/Iset_SCL: R35.2, U10.13, U13.3
/DAC and Current Control/Iset_SDA: R34.2, U10.12, U13.4
/DAC and Current Control/LinearDisable: J15.2, R33.2
/DAC and Current Control/Linear_SCL: R31.2, U10.9, U12.3
/DAC and Current Control/Linear_SDA: R30.2, U10.8, U12.4
/DACCC+5V: C38.1, C39.1, C40.1, C41.1, J12.2, R23.1, R24.1, R26.1, R27.1, R30.1, R31.1, R34.1, R35.1, U10.3, U10.20, U11.2, U11.5, U11.7, U12.2, U12.5, U12.7, U13.2, U13.5, U13.7
/DACCC+12V: C42.2, J12.1, U14.4
/DACCC-12V: C43.2, J12.3, U14.11
/I2C_SCL: J13.2, R23.2, U10.18
/I2C_SDA: J13.1, R24.2, U10.19
/Linear+5V: C49.1, J20.1, U17.4
/Linear-3V3: J20.2, Q5.1
/Linear-5V: C48.2, J20.3, U17.11
/LinearOffset: R50.2, U5.13, U5.14
/LinearRegulator/LinearOutputGND: J22.2, RLY1.COM2
/LinearRegulator/LinearVset: R56.1, U17.8, U17.12
/LinearVout: C52.1, C53.1, J22.1, Q6.3, R59.1, RLY2.NC
/Linear_DAC: R52.2, U14.6, U14.7
/OutputGND: R46.1, R47.1, RLY1.NC2, RLY1.NO1, U16.3
/VCMod+5V: C44.2, C46.2, J16.1, U15.10, U16.4
/VCMod-5V: C45.2, C47.2, J16.2, R41.2, U15.4, U15.5, U16.11
/Vfb-Select: J17.1, R41.1, U15.6
/VoltageADC: J18.1, R45.1, U16.14
/VoltageCurrentModifier/V-Output: R39.1, RLY2.COM
/VoltageCurrentModifier/Vfb+: J19.1, R36.1
/VoltageCurrentModifier/Vfb-: J19.2, R37.2, R38.1, U15.8
/VoltageSelect: J17.2, R2.2
GND: C1.2, C2.2, C4.1, C5.1, C6.2, C7.2, C8.1, C9.1, C10.2, C11.2, C12.1, C13.1, C14.2, C15.2, C16.2, C17.2, C18.2, C19.2, C20.1, C21.1, C22.2, C23.2, C24.1, C25.1, C26.2, C27.2, C28.2, C29.1, C30.1, C31.2, C32.2, C34.2, C35.2, C36.2, C37.1, C38.2, C39.2, C40.2, C41.2, C42.1, C43.1, C44.1, C45.1, C46.1, C47.1, C48.1, C49.2, C50.2, C51.2, C52.2, C53.2, D3.2, D4.2, HS1.1, J1.2, J2.1, J2.2, J2.3, J2.4, J2.5, J10.2, J14.3, J15.3, J21.2, Q1.1, Q2.1, Q3.1, Q4.1, R7.2, R10.2, R12.2, R21.2, R38.2, R40.2, R43.2, R46.2, R47.2, R49.2, R60.2, RLY1.NC1, RLY1.NO2, U1.3, U1.6, U2.2, U3.1, U4.1, U5.3, U6.2, U7.1, U8.4, U9.3, U9.5, U10.1, U10.2, U10.10, U11.8, U12.8, U13.8, U15.7, U17.3, U17.5, U17.10, Vref1.2, Vref2.2, Vref3.2
unnamed: C3.1, U1.2
unnamed: C3.2, U1.4
unnamed: C26.1, POT1.3, R6.2, Vref2.1, Vref2.3
unnamed: C27.1, R8.2, R9.1, Vref3.1, Vref3.3
unnamed: C28.1, R5.2, U5.5, Vref1.1
unnamed: C31.1, C32.1, J10.1, U8.2, U8.7
unnamed: C33.1, D3.1, L1.1, U8.1
unnamed: C33.2, U8.3
unnamed: C50.1, C51.1, HS2.1, J21.1, Q6.2, R58.1
unnamed: D1.2, Q2.3, RLY1.Coil-
unnamed: D2.2, Q1.3, RLY2.Coil-
unnamed: D4.1, J14.1, J15.1, R25.1
unnamed: POT1.1, R7.1
unnamed: POT1.2, U5.10
unnamed: POT2.1, R10.1
unnamed: POT2.2, U5.12
unnamed: POT2.3, R9.2
unnamed: Q1.2, R2.1
unnamed: Q2.2, R1.1
unnamed: Q3.2, R29.1
unnamed: Q3.3, R28.1, U14.3
unnamed: Q4.2, R33.1
unnamed: Q4.3, R32.1, U14.5
unnamed: Q5.2, R57.1
unnamed: Q5.3, Q6.1, R58.2
unnamed: R3.1, R4.2, U5.2
unnamed: R13.1, R14.2, U9.2
unnamed: R14.1, R16.2, U9.1
unnamed: R15.1, R16.1, R17.2, U9.6
unnamed: R17.1, U9.7, U9.10
unnamed: R18.2, R20.2, U9.8
unnamed: R19.1, R22.2, U9.13
unnamed: R20.1, R21.1, U9.12
unnamed: R22.1, U9.9, U9.14
unnamed: R25.2, U14.14
unnamed: R28.2, U11.6
unnamed: R32.2, U12.6
unnamed: R36.2, R37.1, U15.1
unnamed: R39.2, R40.1, U15.3
unnamed: R42.1, R43.1, U16.12
unnamed: R42.2, U16.6, U16.7
unnamed: R44.1, R45.2, U16.13
unnamed: R44.2, U16.8, U16.9
unnamed: R48.2, R49.1, U16.2
unnamed: R50.1, R51.2, U17.2
unnamed: R51.1, R53.2, U17.1
unnamed: R52.1, R53.1, R54.2, U17.6
unnamed: R54.1, R55.2, U17.7
unnamed: R55.1, R56.2, U17.9
unnamed: R57.2, U17.14
unnamed: R59.2, R60.1, U17.13
unnamed: U13.6, U14.10
unnamed: U15.2, U16.5
unnamed: U15.9, U16.10
